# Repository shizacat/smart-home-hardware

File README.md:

# Description

Hardware for smart home (homebridge) on RPi Zero W.

Modules:
- Raspberry Pi Zero W
- ZigBee module from [RF start CC2652P](https://aliexpress.ru/item/1005002460600394.html)

# Hardware

The project created in [Eagle](https://www.autodesk.com/products/eagle/overview).

# Software

https://github.com/shizacat/smart-home

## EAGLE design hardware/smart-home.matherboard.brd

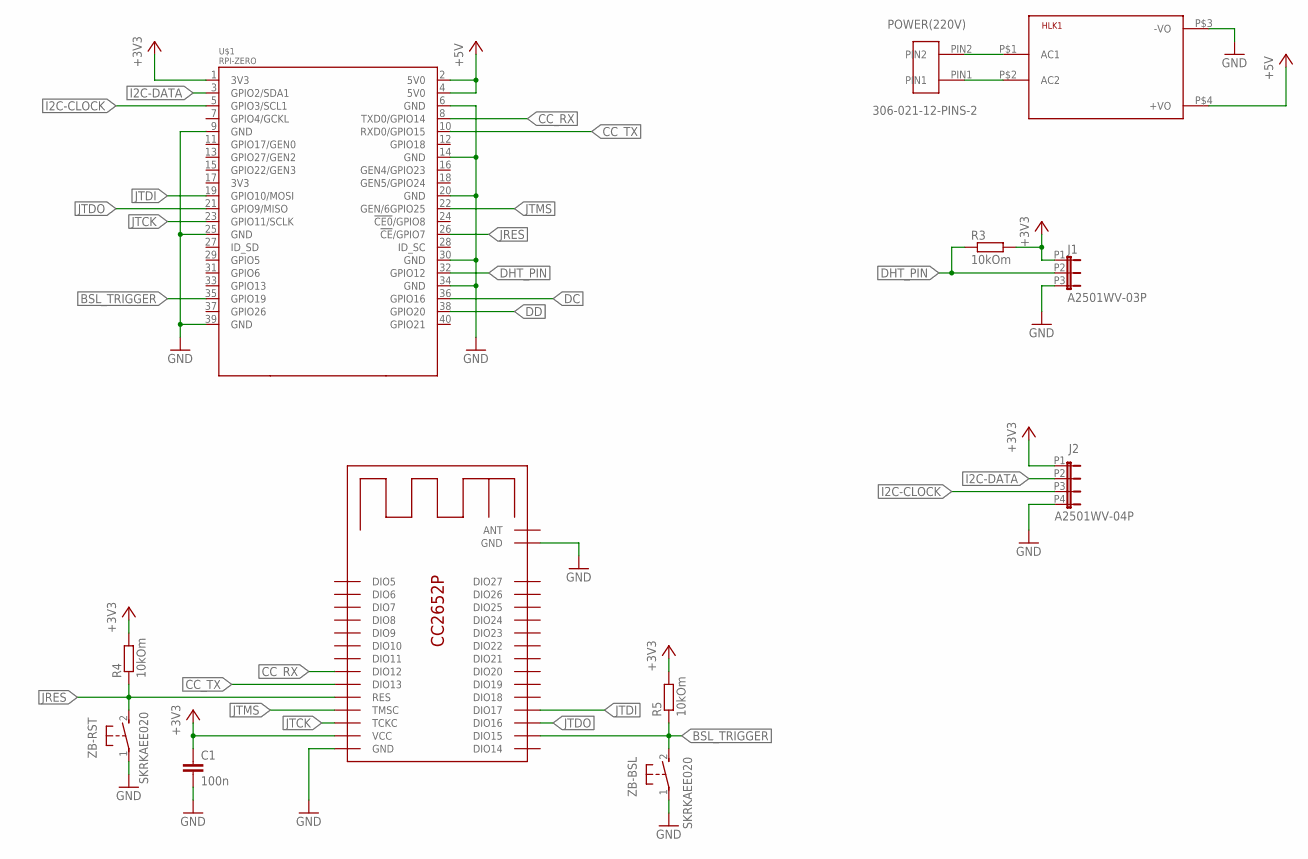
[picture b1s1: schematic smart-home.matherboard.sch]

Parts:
C1: 100n; C0603K
HLK1: HLK-PM013W; HLK-PM01
J1: A2501WV-03P
J2: A2501WV-04P
POWER(220V): 306-021-12-PINS-2; SERIA-306-2PIN
R3, R4, R5: 10kOm; R0603
U1: CC2652P2-DUOWEISI; CC2653P2-DUOWEISI
U$1: RPI-ZERO; RASPBERRYPI_BASTELSTUBE_V13_RASPI_BOARD_B+_FULL
ZB-BSL: SKRKAEE020
ZB-RST: SKRKAEE020

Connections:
+3V3: C1.1, J1.P1 (1), J2.P1 (1), R3.2, R4.2, R5.2, U1.VCC, U$1.1 (3V3)
+5V: HLK1.P$4 (+VO), U$1.2 (5V0), U$1.4 (5V0)
BSL_TRIGGER: R5.1, U1.DIO15, U$1.35 (GPIO19), ZB-BSL.2
CC_RX: U1.DIO12, U$1.8 (TXD0/GPIO14)
CC_TX: U1.DIO13, U$1.10 (RXD0/GPIO15)
DC: U$1.36 (GPIO16)
DD: U$1.38 (GPIO20)
DHT_PIN: J1.P2 (2), R3.1, U$1.32 (GPIO12)
GND: C1.2, HLK1.P$3 (-VO), J1.P3 (3), J2.P4 (4), U1.GND, U1.GND@1 (GND), U$1.6 (GND), U$1.9 (GND), U$1.14 (GND), U$1.20 (GND), U$1.25 (GND), U$1.30 (GND), U$1.34 (GND), U$1.39 (GND), ZB-BSL.1, ZB-RST.1
I2C-CLOCK: J2.P3 (3), U$1.5 (GPIO3/SCL1)
I2C-DATA: J2.P2 (2), U$1.3 (GPIO2/SDA1)
JRES: R4.1, U1.RES, U$1.26 (!CE!/GPIO7), ZB-RST.2
JTCK: U1.TCKC, U$1.23 (GPIO11/SCLK)
JTDI: U1.DIO17, U$1.19 (GPIO10/MOSI)
JTDO: U1.DIO16, U$1.21 (GPIO9/MISO)
JTMS: U1.TMSC, U$1.22 (GEN/6GPIO25)
unnamed: HLK1.P$1 (AC1), POWER(220V).PIN2
unnamed: HLK1.P$2 (AC2), POWER(220V).PIN1

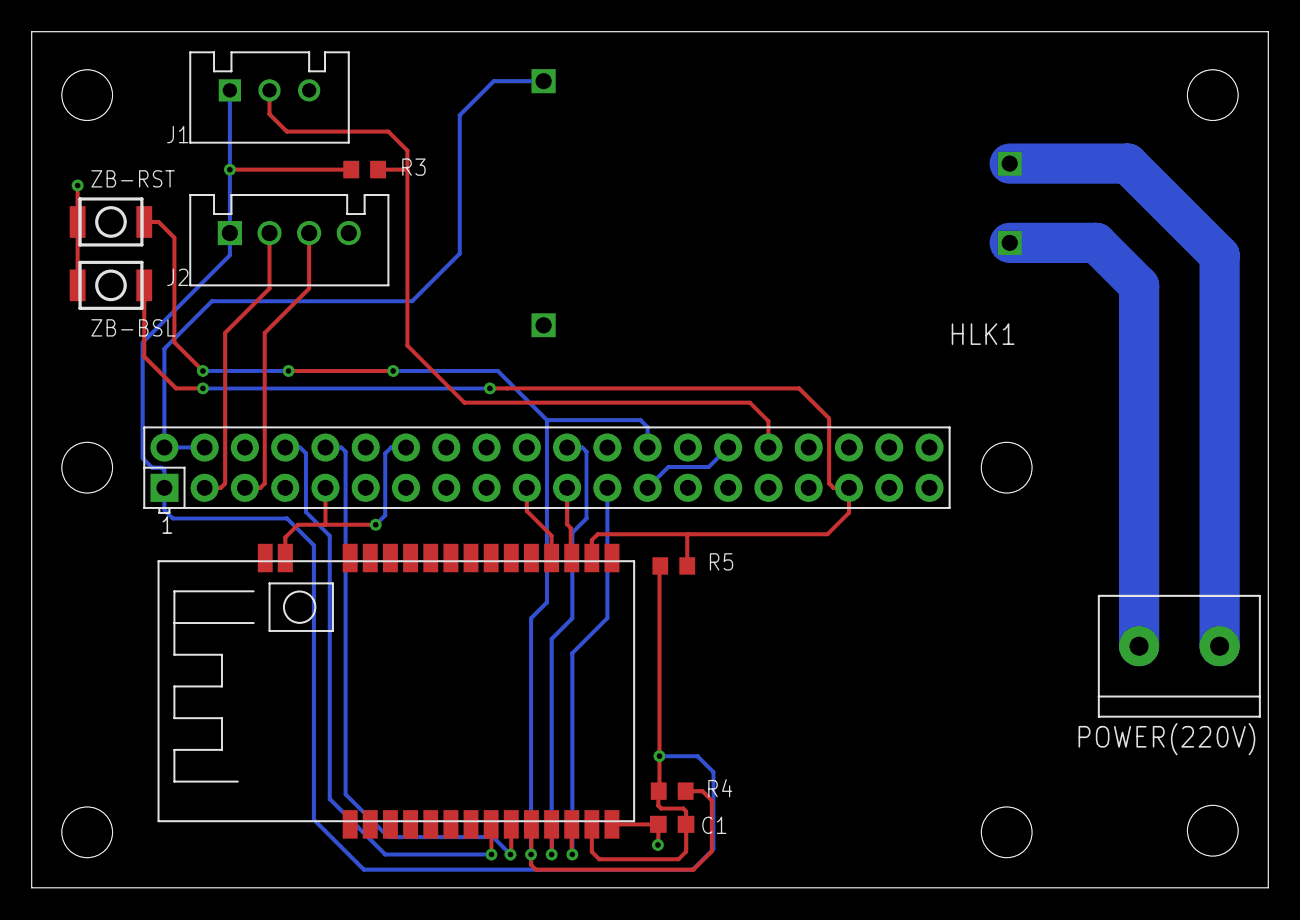
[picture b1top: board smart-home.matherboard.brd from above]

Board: 2 copper layers, 78.0 x 54.0 mm, 13 parts (0 on the bottom side), 16 nets.

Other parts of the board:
DRILEGEND: DRILEGEND

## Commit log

2021-11-08 First version
2021-11-18 Prepea
2021-12-29 update schema
2021-12-29 Move to separete folder
2021-12-29 Add README.md
2022-01-15 Add buttons for reset and flash
2022-01-15 Set all diameter of holes to 3.2
2022-01-15 Add name of connectors
